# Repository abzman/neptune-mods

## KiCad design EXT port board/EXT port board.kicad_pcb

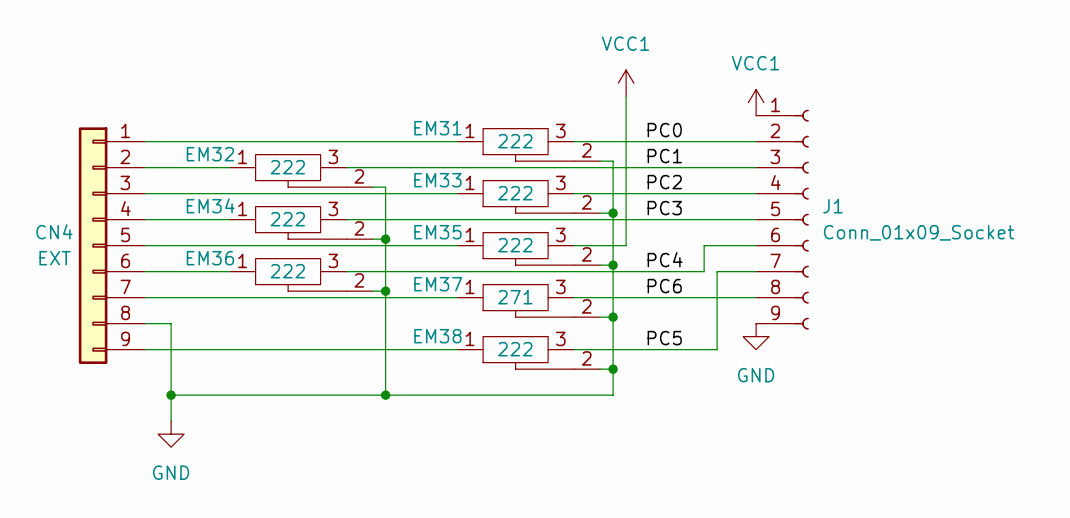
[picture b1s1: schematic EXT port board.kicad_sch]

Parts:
CN4: EXT; DSUB-9_Socket_Horizontal_P2.77x2.84mm_EdgePinOffset7.70mm_H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
EM31, EM32, EM33, EM34, EM35, EM36, EM38: 222; EMI_3P
EM37: 271; EMI_3P
J1: Conn_01x09_Socket; PinHeader_1x09_P2.00mm_Vertical

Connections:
/PC0: EM31.3, J1.2
/PC1: EM32.3, J1.3
/PC2: EM33.3, J1.4
/PC3: EM34.3, J1.5
/PC4: EM36.3, J1.6
/PC5: EM38.3, J1.7
/PC6: EM37.3, J1.8
GND: CN4.8, EM31.2, EM32.2, EM33.2, EM34.2, EM35.2, EM36.2, EM37.2, EM38.2, J1.9
unnamed: CN4.1, EM31.1
unnamed: CN4.2, EM32.1
unnamed: CN4.3, EM33.1
unnamed: CN4.4, EM34.1
unnamed: CN4.5, EM35.1
unnamed: CN4.6, EM36.1
unnamed: CN4.7, EM37.1
unnamed: CN4.9, EM38.1
VCC1: EM35.3, J1.1

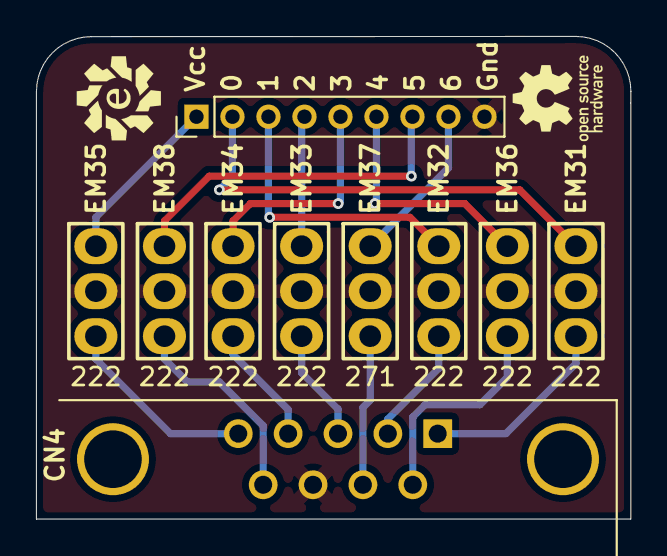
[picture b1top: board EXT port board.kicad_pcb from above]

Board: 2 copper layers, 33.0 x 26.8 mm, 10 parts (0 on the bottom side), 17 nets.

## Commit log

2026-04-27 first design
